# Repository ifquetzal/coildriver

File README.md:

# coildriver
Electronic circuit fast current swicthing with inductive loads.

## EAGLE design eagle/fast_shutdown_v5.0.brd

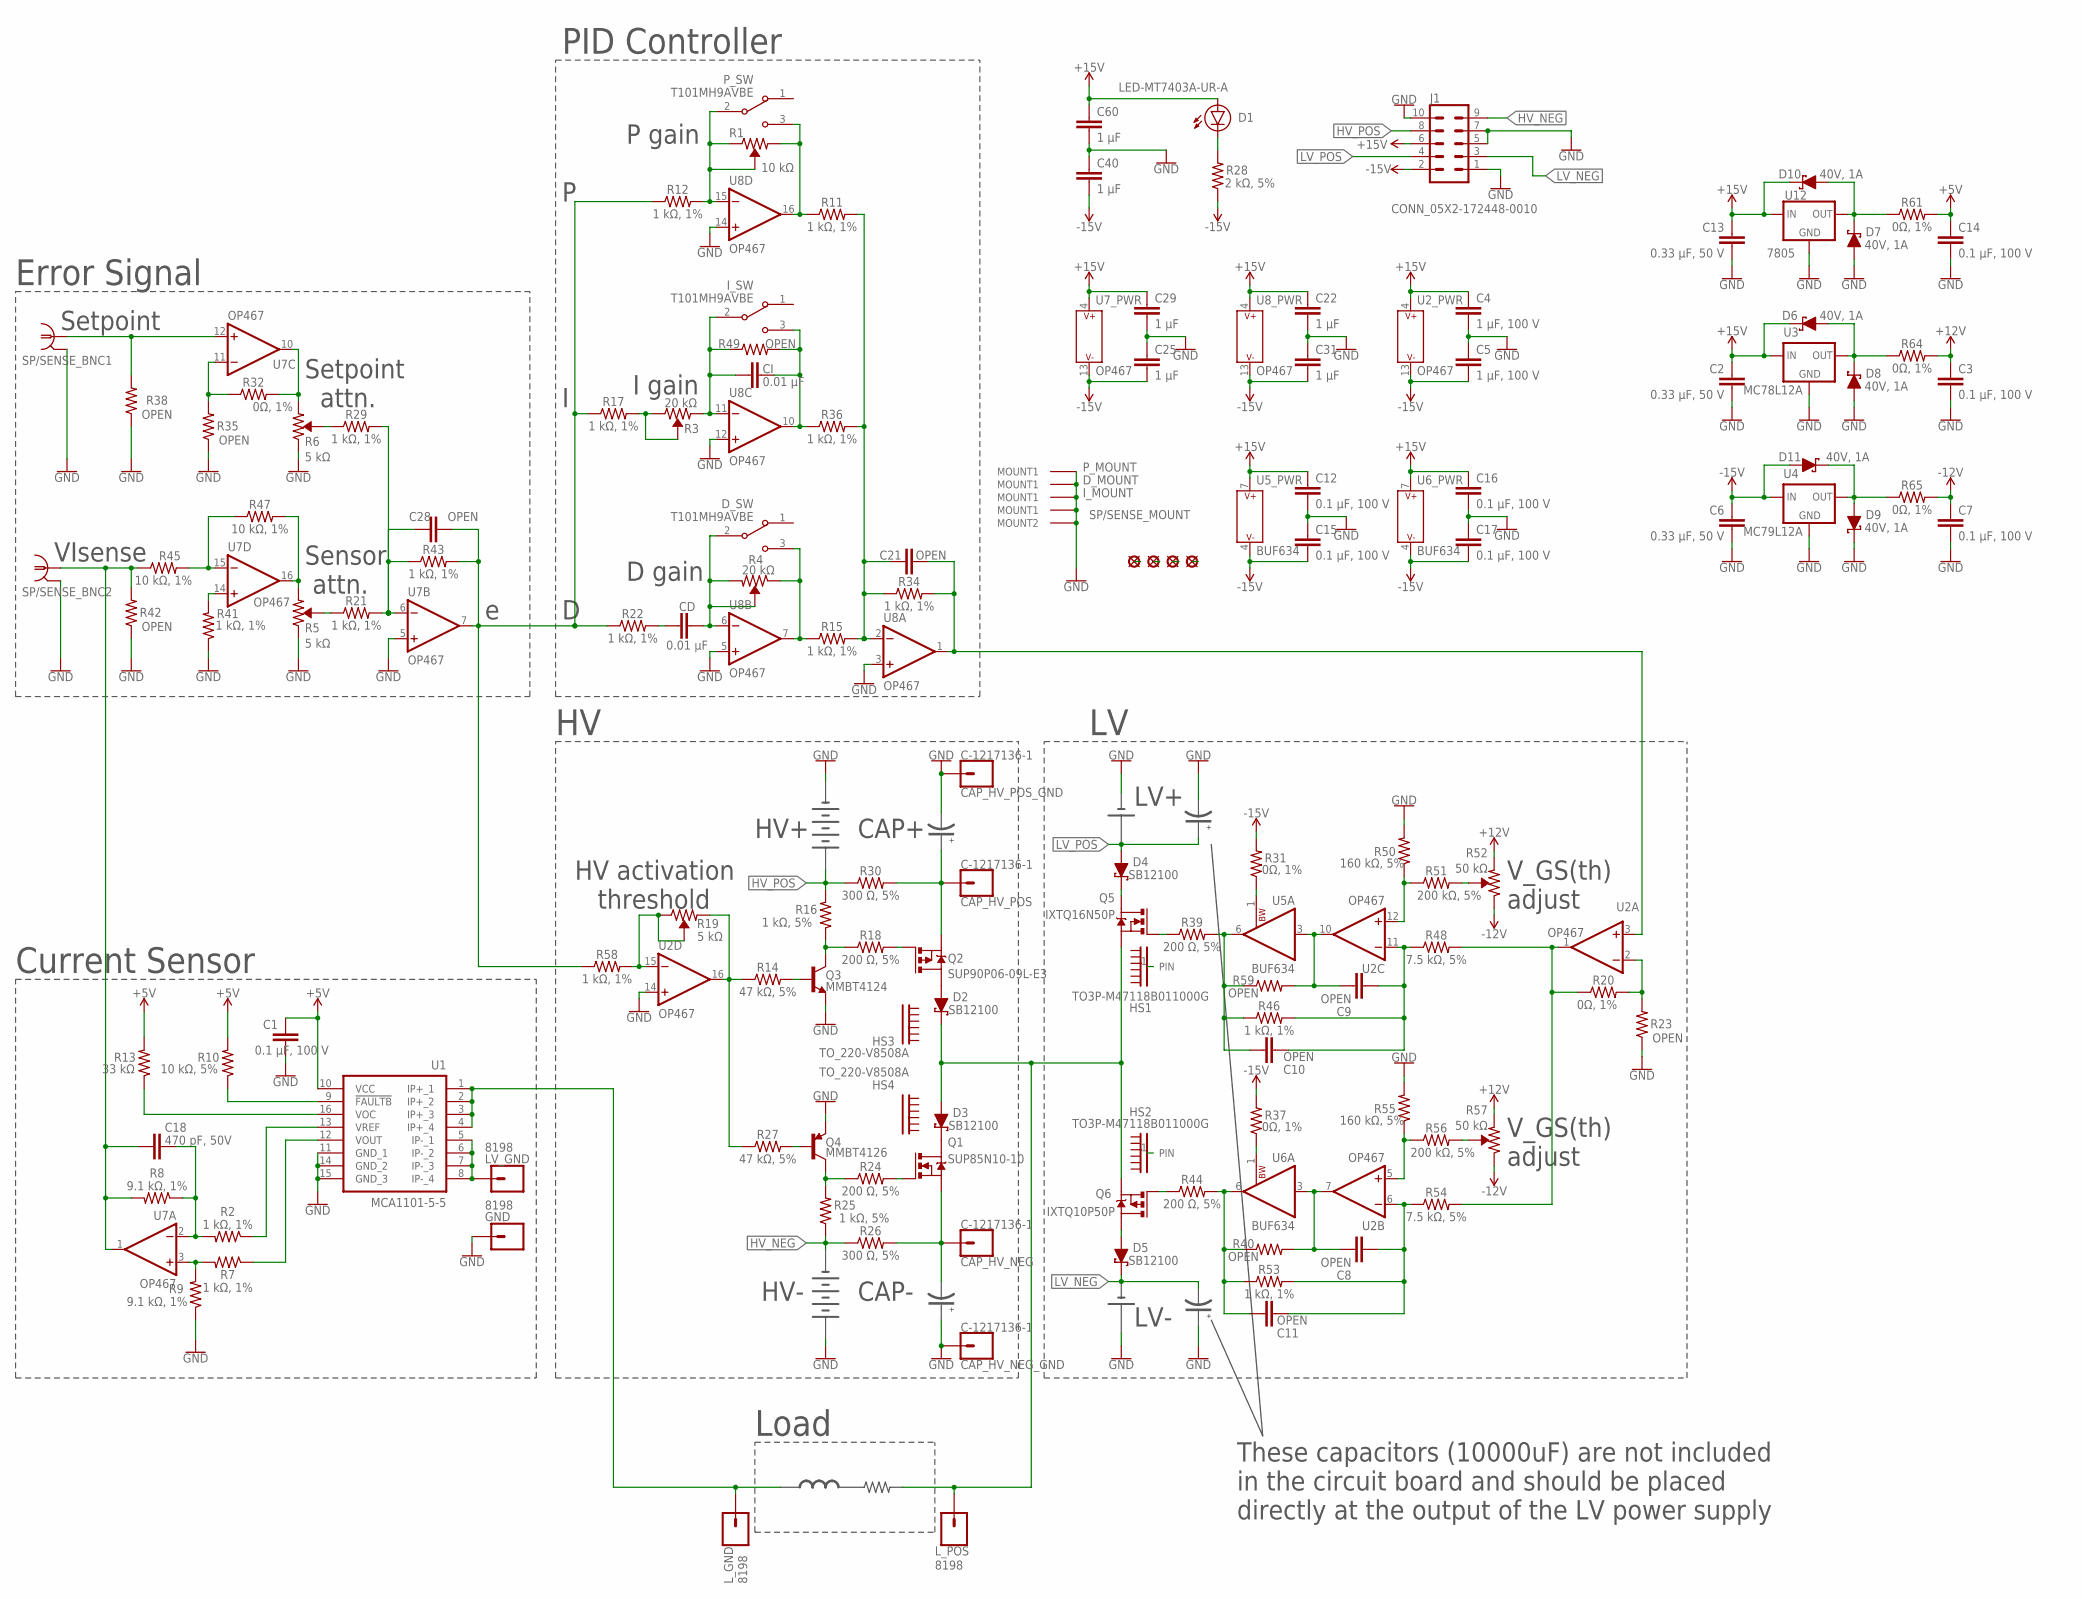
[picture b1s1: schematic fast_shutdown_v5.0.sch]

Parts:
C1, C3, C7, C12, C14, C15, C16, C17: 0.1 µF, 100 V; C1206
C2, C6, C13: 0.33 µF, 50 V; C1206
C4, C5: 1 µF, 100 V; C1206
C8, C9, C10, C11, C21, C28: OPEN; C1206_OPEN
C18: 470 pF, 50V; C1206
C22, C25, C29, C31, C40, C60: 1 µF; C1206
CAP_HV_NEG: C-1217136-1
CAP_HV_NEG_GND: C-1217136-1
CAP_HV_POS: C-1217136-1
CAP_HV_POS_GND: C-1217136-1
CD: 0.01 µF; C1206
CI: 0.01 µF; C1206
D: T101MH9AVBE
D1: LED-MT7403A-UR-A; LED3MM
D2, D3, D4, D5: SB12100; D5.4X7.5
D6, D7, D8, D9, D10, D11: 40V, 1A; DO-214AC
GND: 8198
HS1, HS2: TO3P-M47118B011000G; M47118B011000G
HS3, HS4: TO_220-V8508A; V8508A
I: T101MH9AVBE
J1: CONN_05X2-172448-0010; 1724480010
LV_GND: 8198
L_GND: 8198
L_POS: 8198
P: T101MH9AVBE
P1, P2, P3, P4: PAD-M3.0; PAD_M3.0
Q1: SUP85N10-10; TO220AB_BL
Q2: SUP90P06-09L-E3; TO220AB_BL
Q3: MMBT4124; SOT23
Q4: MMBT4126; SOT23
Q5: IXTQ16N50P; TO3P
Q6: IXTQ10P50P; TO3P
R1: 10 kΩ; POT_3006P
R2, R7, R11, R12, R15, R17, R21, R22, R29, R34, R36, R41, R43, R46, R53, R58: 1 kΩ, 1%; R1206
R3, R4: 20 kΩ; POT_3006P
R5, R6, R19: 5 kΩ; POT_3006P
R8, R9: 9.1 kΩ, 1%; R1206
R10: 10 kΩ, 5%; R1206
R13: 33 kΩ; R1206
R14, R27: 47 kΩ, 5%; R1206
R16, R25: 1 kΩ, 5%; R1206
R18, R24, R39, R44: 200 Ω, 5%; R1206
R20, R31, R32, R37, R61, R64, R65: 0Ω, 1%; R1206
R23, R35, R38, R40, R42, R49, R59: OPEN; R1206_OPEN
R26, R30: 300 Ω, 5%; R1206
R28: 2 kΩ, 5%; R1206
R45, R47: 10 kΩ, 1%; R1206
R48, R54: 7.5 kΩ, 5%; R1206
R50, R55: 160 kΩ, 5%; R1206
R51, R56: 200 kΩ, 5%; R1206
R52, R57: 50 kΩ; POT_3006P
SP/SENSE: BNC2_CHG-5227161-1; 5227161-1_CHG
U1: MCA1101-5-5; SOIC16-W
U2, U7, U8: OP467; SOIC16-W
U3: MC78L12A; SOIC8-N
U4: MC79L12A; SOIC8-N
U5, U6: BUF634; SOIC8-N
U12: 7805; DPAK

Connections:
+5V: C1.1, C14.1, R10.2, R13.2, R61.2, U1.10 (VCC)
+12V: C3.1, R52.1 (CCW), R57.1 (CCW), R64.2
+15V: C2.1, C4.1, C12.1, C13.1, C16.1, C22.1, C29.1, C60.1, D1.A, D6.K (C), D10.K (C), J1.6, U2.4 (P$V+), U3.8 (IN), U5.7 (P$V+), U6.7 (P$V+), U7.4 (P$V+), U8.4 (P$V+), U12.1 (IN)
-12V: C7.1, R52.3 (CW), R57.3 (CW), R65.2
-15V: C5.2, C6.1, C15.2, C17.2, C25.2, C31.2, C40.2, D11.A, J1.2, R28.1, R31.2, R37.2, U2.13 (P$V-), U4.2 (IN), U4.3 (IN), U4.6 (IN), U4.7 (IN), U5.4 (P$V-), U6.4 (P$V-), U7.13 (P$V-), U8.13 (P$V-)
CAP_HV_NEG: CAP_HV_NEG.1, CAP_HV_NEG.2, Q1.3 (S), R26.2
CAP_HV_POS: CAP_HV_POS.1, CAP_HV_POS.2, Q2.3 (S), R30.2
GND: C1.2, C2.2, C3.2, C4.2, C5.1, C6.2, C7.2, C12.2, C13.2, C14.2, C15.1, C16.2, C17.1, C22.2, C25.1, C29.2, C31.1, C40.1, C60.2, CAP_HV_NEG_GND.1, CAP_HV_NEG_GND.2, CAP_HV_POS_GND.1, CAP_HV_POS_GND.2, D.H1 (MOUNT1), D7.A, D8.A, D9.K (C), GND.1, GND.2, I.H1 (MOUNT1), J1.1, J1.5, J1.7, J1.10, P.H1 (MOUNT1), Q3.2 (E), Q4.2 (E), R5.3 (CW), R6.3 (CW), R9.1, R23.1, R35.1, R38.1, R41.1, R42.1, R50.2, R55.2, SP/SENSE.2, SP/SENSE.4 (2), SP/SENSE.H1 (MOUNT1), SP/SENSE.H2 (MOUNT2), SP/SENSE.H3 (MOUNT1), SP/SENSE.H5 (MOUNT1), SP/SENSE.H6 (MOUNT2), U1.11 (GND_1), U1.14 (GND_2), U1.15 (GND_3), U2.14 (+IN), U3.2 (GND), U3.3 (GND), U3.6 (GND), U3.7 (GND), U4.5 (GND), U7.5 (+IN), U8.3 (+IN), U8.5 (+IN), U8.12 (+IN), U8.14 (+IN), U12.4 (GND)
HV_NEG: J1.9, R25.1, R26.1
HV_POS: J1.8, R16.2, R30.1
LV_NEG: D5.1 (C), J1.3
LV_POS: D4.2 (A), J1.4
unnamed: C18.2, R8.2, R42.2, R45.1, SP/SENSE.3 (1), U7.1 (OUT)
unnamed: R45.2, R47.1, U7.15 (-IN)
unnamed: R5.1 (CCW), R47.2, U7.16 (OUT)
unnamed: D.3 (NO), R4.3 (CW), R15.1, U8.7 (OUT)
unnamed: C21.2, R34.2, U2.3 (+IN), U8.1 (OUT)
unnamed: R41.2, U7.14 (+IN)
unnamed: R5.2 (WIPER), R21.1
unnamed: C28.1, R21.2, R29.2, R43.1, U7.6 (-IN)
unnamed: P1.1 (H), P1.2 (H), P1.3 (H), P1.4 (H), P1.5 (H), P1.6 (H), P1.7 (H), P1.8 (H), P1.P
unnamed: R32.1, R35.2, U7.11 (-IN)
unnamed: R6.1 (CCW), R32.2, U7.10 (OUT)
unnamed: R6.2 (WIPER), R29.1
unnamed: L_GND.1, L_GND.2, U1.1 (IP+_1), U1.2 (IP+_2), U1.3 (IP+_3), U1.4 (IP+_4)
unnamed: C21.1, R11.2, R15.2, R34.1, R36.2, U8.2 (-IN)
unnamed: Q3.3 (C), R16.1, R18.1
unnamed: R2.1, U1.13 (VREF)
unnamed: R7.1, U1.12 (VOUT)
unnamed: R20.1, R48.2, R54.2, U2.1 (OUT)
unnamed: LV_GND.1, LV_GND.2, U1.5 (IP-_1), U1.6 (IP-_2), U1.7 (IP-_3), U1.8 (IP-_4)
unnamed: R20.2, R23.2, U2.2 (-IN)
unnamed: C28.2, R12.1, R17.1, R22.1, R43.2, R58.1, U7.7 (OUT)
unnamed: R38.2, SP/SENSE.1, U7.12 (+IN)
unnamed: P2.1 (H), P2.2 (H), P2.3 (H), P2.4 (H), P2.5 (H), P2.6 (H), P2.7 (H), P2.8 (H), P2.P
unnamed: D2.1 (C), D3.2 (A), L_POS.1, L_POS.2, Q5.3 (S), Q6.3 (S)
unnamed: P.2 (COMMON), R1.2 (WIPER), R1.3 (CW), R12.2, U8.15 (-IN)
unnamed: P.3 (NO), R1.1 (CCW), R11.1, U8.16 (OUT)
unnamed: C10.2, R39.2, R46.1, R59.1, U5.6 (OUT)
unnamed: CI.1, I.2 (COMMON), R3.1 (CCW), R49.1, U8.11 (-IN)
unnamed: CI.2, I.3 (NO), R36.1, R49.2, U8.10 (OUT)
unnamed: R3.2 (WIPER), R3.3 (CW), R17.2
unnamed: CD.2, D.2 (COMMON), R4.1 (CCW), R4.2 (WIPER), U8.6 (-IN)
unnamed: CD.1, R22.2
unnamed: C9.2, R59.2, U2.10 (OUT), U5.3 (IN)
unnamed: C8.2, R40.2, U2.7 (OUT), U6.3 (IN)
unnamed: R31.1, U5.1 (BW)
unnamed: R37.1, U6.1 (BW)
unnamed: D1.K (C), R28.2
unnamed: D7.K (C), D10.A, R61.1, U12.3 (OUT)
unnamed: D6.A, D8.K (C), R64.1, U3.1 (OUT)
unnamed: D9.A, D11.K (C), R65.1, U4.1 (OUT)
unnamed: P3.1 (H), P3.2 (H), P3.3 (H), P3.4 (H), P3.5 (H), P3.6 (H), P3.7 (H), P3.8 (H), P3.P
unnamed: P4.1 (H), P4.2 (H), P4.3 (H), P4.4 (H), P4.5 (H), P4.6 (H), P4.7 (H), P4.8 (H), P4.P
unnamed: R50.1, R51.1, U2.12 (+IN)
unnamed: C18.1, R2.2, R8.1, U7.2 (-IN)
unnamed: R7.2, R9.2, U7.3 (+IN)
unnamed: R10.1, U1.9 (!FAULTB)
unnamed: R13.1, U1.16 (VOC)
unnamed: Q3.1 (B), R14.2
unnamed: Q2.1 (G), R18.2
unnamed: D5.2 (A), Q6.2 (D)
unnamed: D2.2 (A), Q2.2 (D)
unnamed: D3.1 (C), Q1.2 (D)
unnamed: Q1.1 (G), R24.2
unnamed: Q4.3 (C), R24.1, R25.2
unnamed: Q4.1 (B), R27.2
unnamed: D4.1 (C), Q5.2 (D)
unnamed: Q6.1 (G), R44.1
unnamed: Q5.1 (G), R39.1
unnamed: C9.1, C10.1, R46.2, R48.1, U2.11 (-IN)
unnamed: R51.2, R52.2 (WIPER)
unnamed: C8.1, C11.1, R53.2, R54.1, U2.6 (-IN)
unnamed: R55.1, R56.1, U2.5 (+IN)
unnamed: R56.2, R57.2 (WIPER)
unnamed: C11.2, R40.1, R44.2, R53.1, U6.6 (OUT)
unnamed: R19.2 (WIPER), R19.3 (CW), R58.2, U2.15 (-IN)
unnamed: R14.1, R19.1 (CCW), R27.1, U2.16 (OUT)

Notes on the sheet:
Load
Current Sensor
Error Signal
PID Controller
These capacitors (10000uF) are not included in the circuit board and should be placed directly at the output of the LV power supply
Setpoint
VIsense
Setpoint attn.
Sensor attn.
P gain
I gain
D gain
HV activation threshold
V_GS(th) adjust
V_GS(th) adjust
HV-
HV+
CAP+
CAP-
LV+
LV-

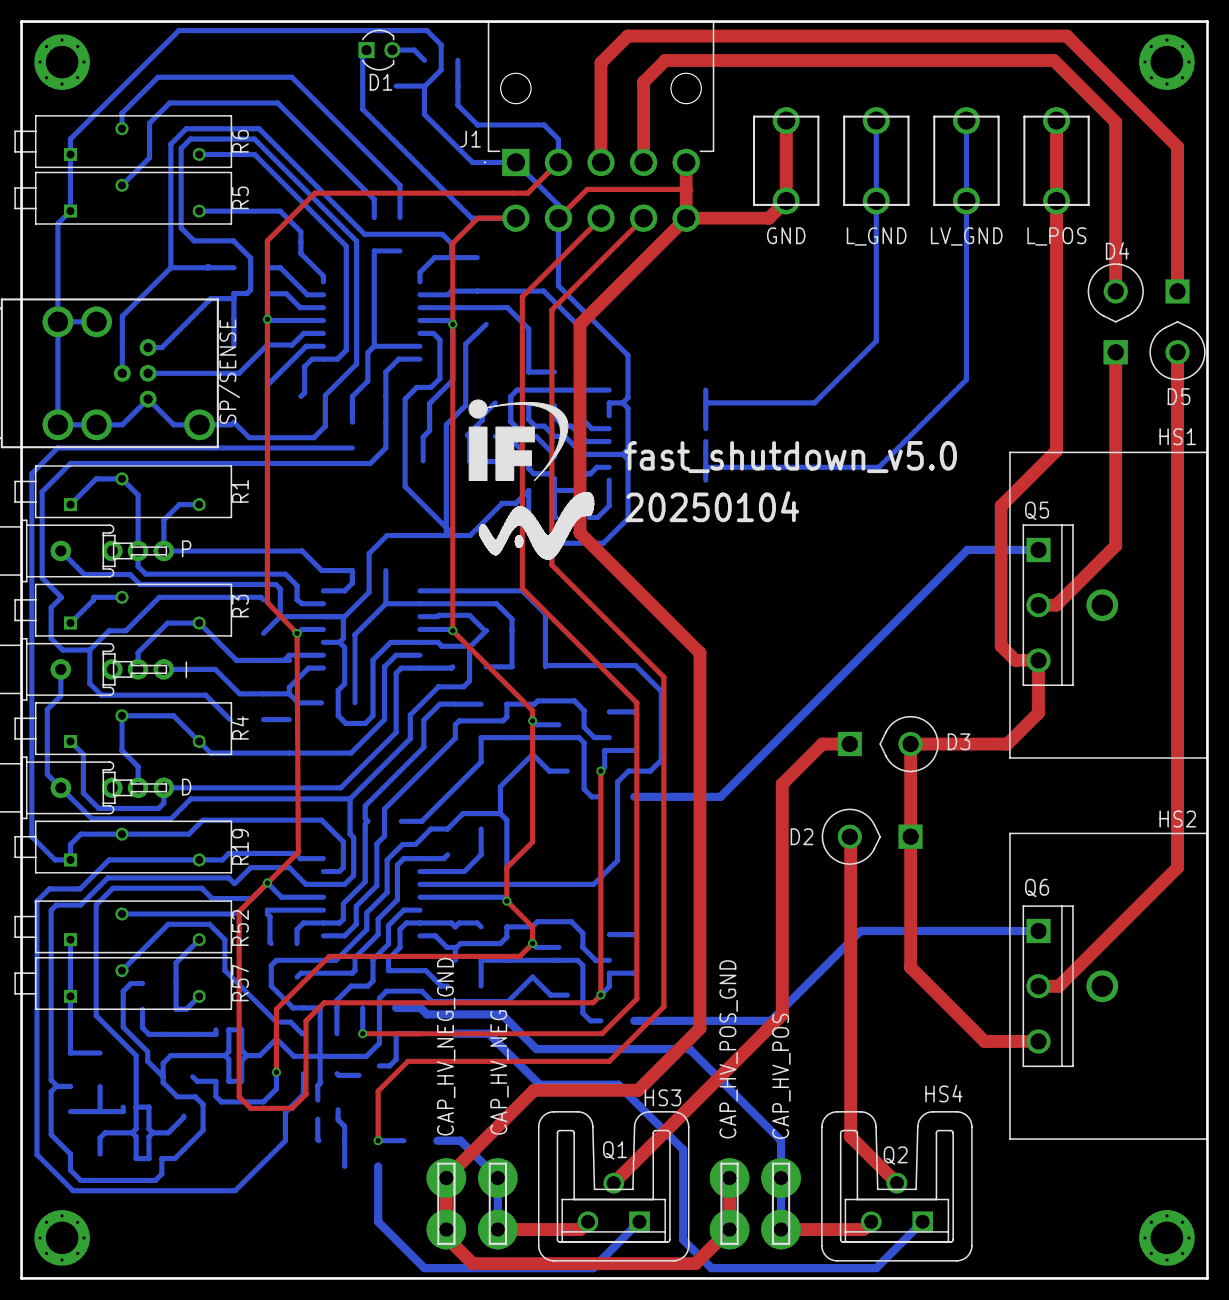
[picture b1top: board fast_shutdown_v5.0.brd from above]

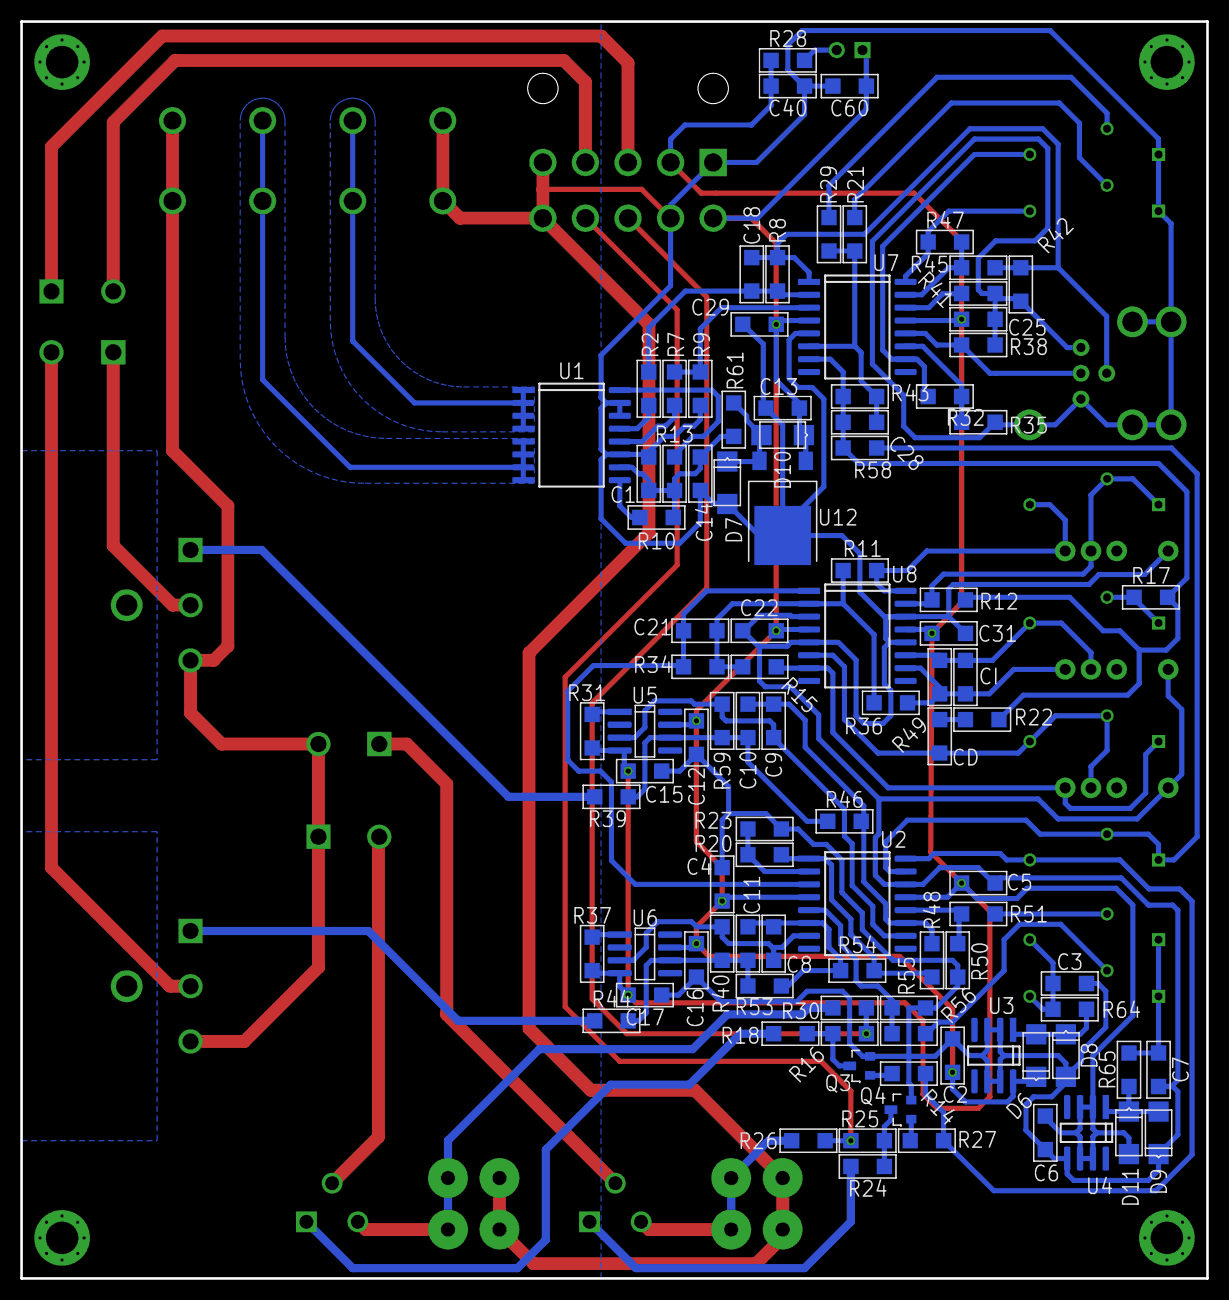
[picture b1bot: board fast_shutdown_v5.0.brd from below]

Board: 2 copper layers, 117.0 x 124.0 mm, 138 parts (98 on the bottom side), 78 nets.

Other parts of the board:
U$87: IFUNAM
U$88: LANMAC_2.0

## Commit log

2025-03-27 adding Autodesk Eagle files
2025-03-27 adding .PDF schematic
